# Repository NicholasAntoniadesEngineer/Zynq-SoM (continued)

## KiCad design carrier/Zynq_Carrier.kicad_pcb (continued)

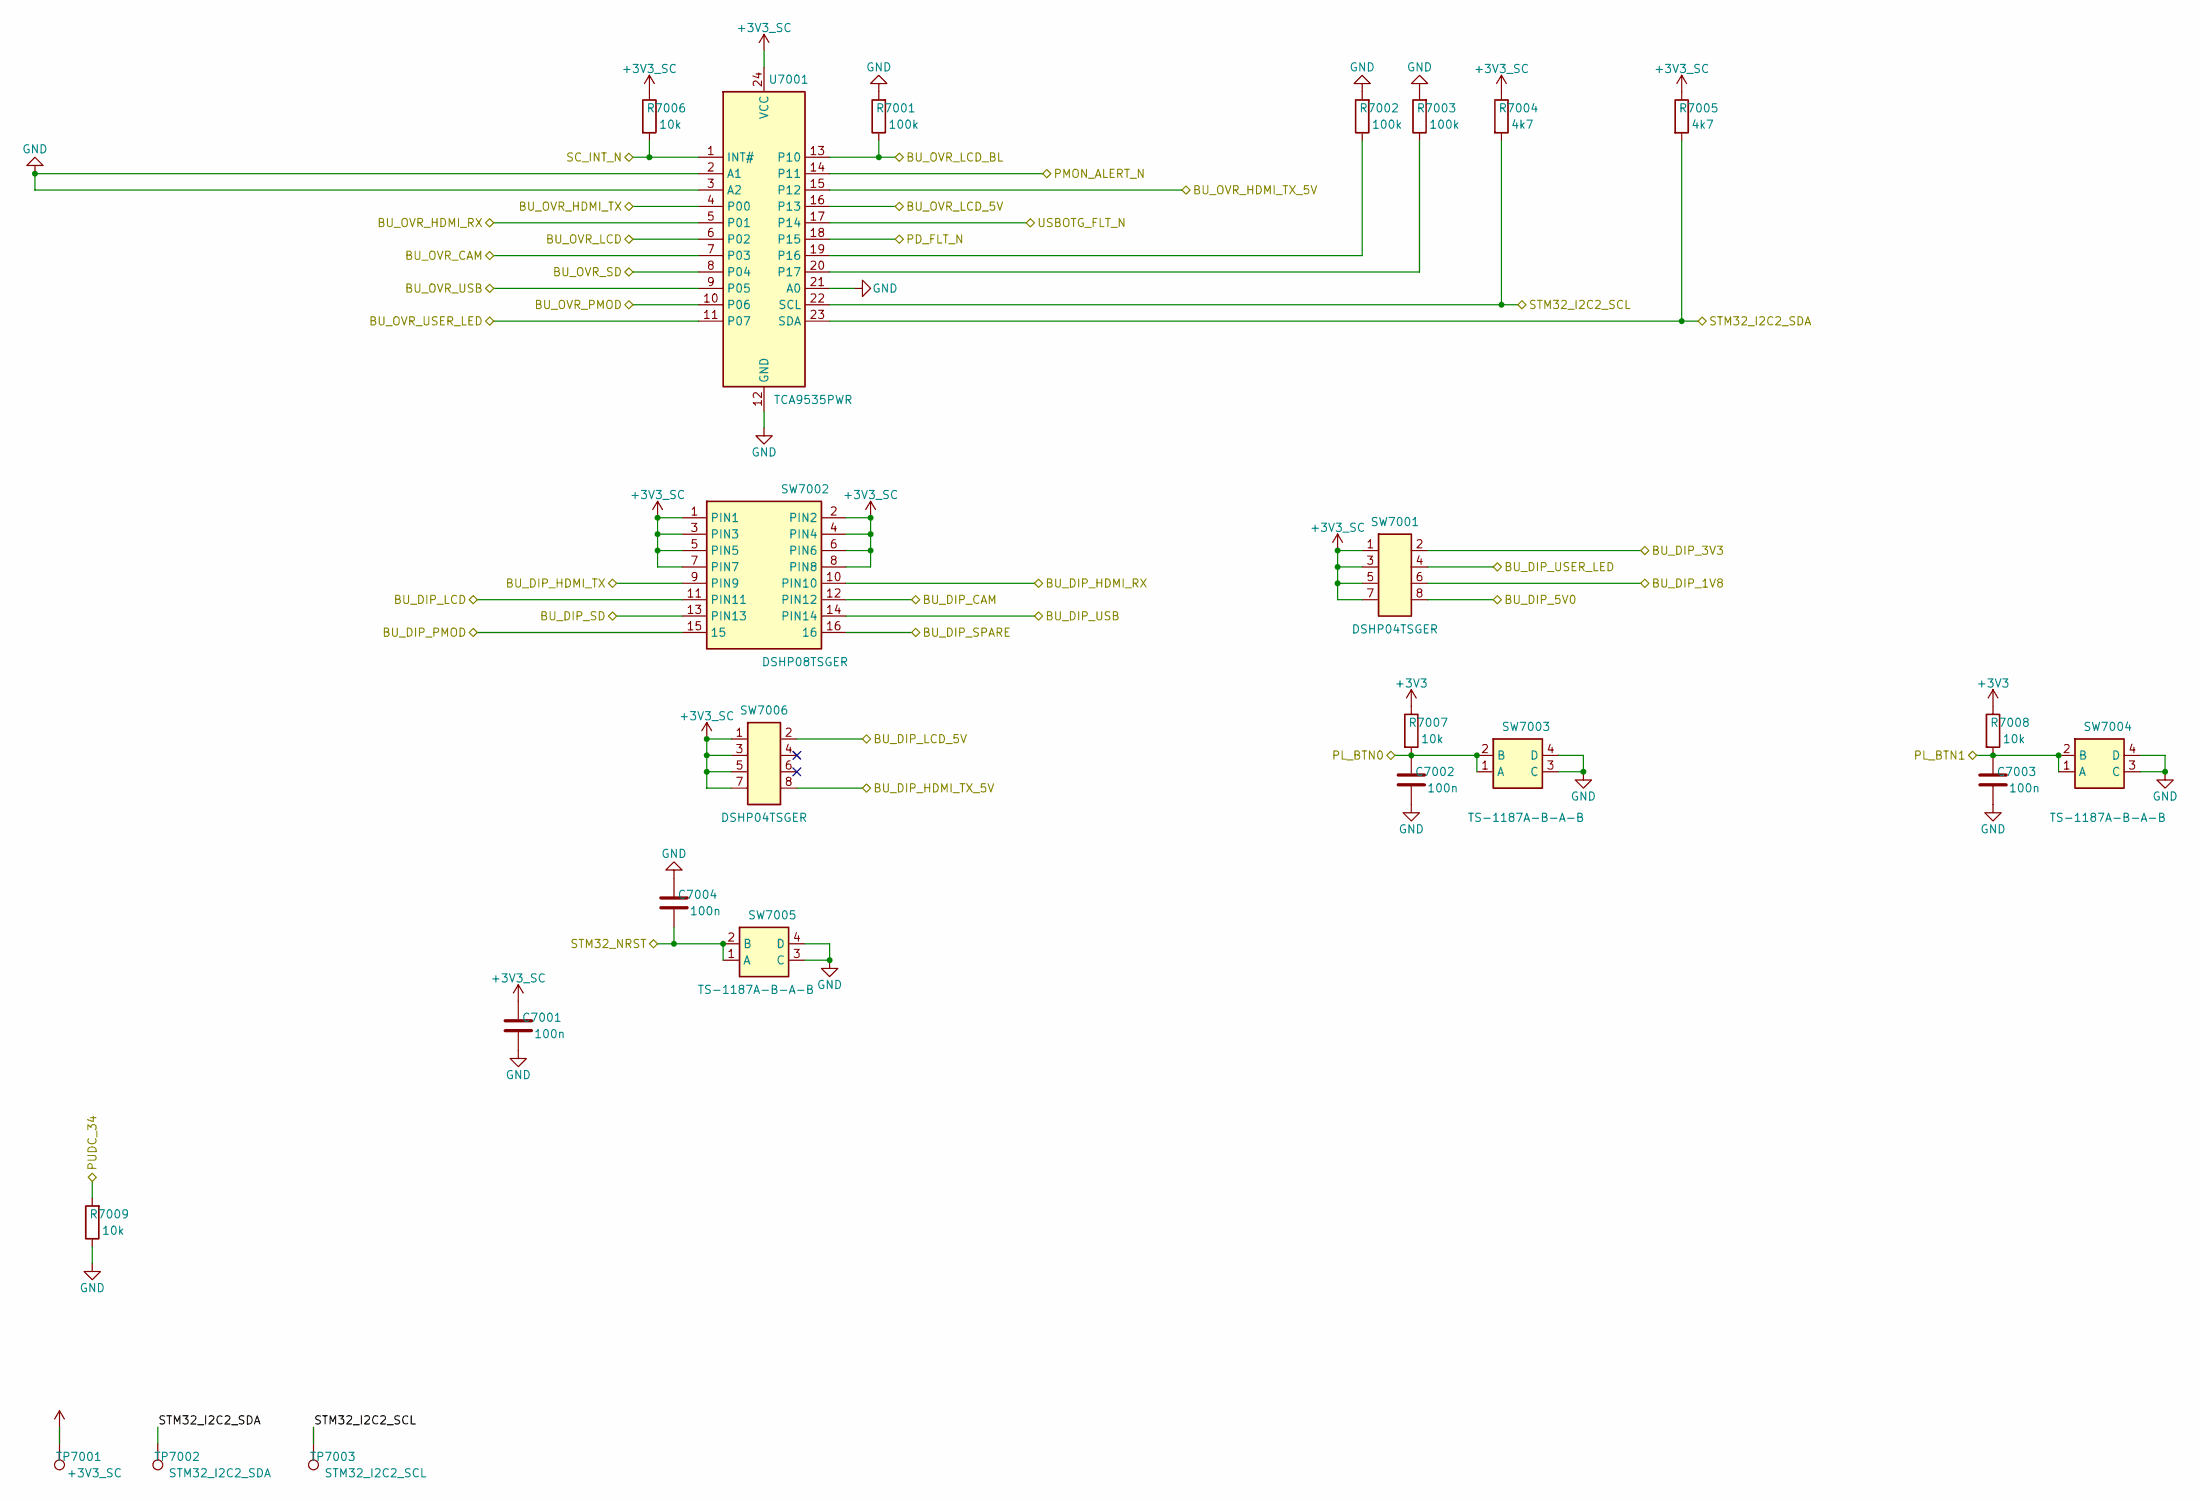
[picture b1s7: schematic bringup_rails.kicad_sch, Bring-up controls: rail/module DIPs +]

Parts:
C7001, C7002, C7003, C7004: 100n; C_0603_1608Metric; LCSC C14663
R7001, R7002, R7003: 100k; R_0603_1608Metric; LCSC C25803
R7004, R7005: 4k7; R_0603_1608Metric; LCSC C23162
R7006, R7007, R7008, R7009: 10k; R_0603_1608Metric; LCSC C25804
SW7001, SW7006: DSHP04TSGER; LCSC C3293144
SW7002: DSHP08TSGER; LCSC C3293147
SW7003, SW7004, SW7005: TS-1187A-B-A-B; LCSC C318884
TP7001: +3V3_SC; TestPoint_Pad_D1.5mm
TP7002: STM32_I2C2_SDA; TestPoint_Pad_D1.5mm
TP7003: STM32_I2C2_SCL; TestPoint_Pad_D1.5mm
U7001: TCA9535PWR; LCSC C130204

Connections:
+3V3: R7007.1, R7008.1; also elsewhere on the board
+3V3_SC: C7001.1, R7004.1, R7005.1, R7006.1, SW7001.1, SW7001.3, SW7001.5, SW7001.7, SW7002.1 (PIN1), SW7002.2 (PIN2), SW7002.3 (PIN3), SW7002.4 (PIN4), SW7002.5 (PIN5), SW7002.6 (PIN6), SW7002.7 (PIN7), SW7002.8 (PIN8), SW7006.1, SW7006.3, SW7006.5, SW7006.7, TP7001.1, U7001.24 (VCC); also elsewhere on the board
BU_DIP_1V8: SW7001.6; also elsewhere on the board
BU_DIP_3V3: SW7001.2; also elsewhere on the board
BU_DIP_5V0: SW7001.8; also elsewhere on the board
BU_DIP_CAM: SW7002.12 (PIN12); also elsewhere on the board
BU_DIP_HDMI_RX: SW7002.10 (PIN10); also elsewhere on the board
BU_DIP_HDMI_TX: SW7002.9 (PIN9); also elsewhere on the board
BU_DIP_HDMI_TX_5V: SW7006.8; also elsewhere on the board
BU_DIP_LCD: SW7002.11 (PIN11); also elsewhere on the board
BU_DIP_LCD_5V: SW7006.2; also elsewhere on the board
BU_DIP_PMOD: SW7002.15; also elsewhere on the board
BU_DIP_SD: SW7002.13 (PIN13); also elsewhere on the board
BU_DIP_SPARE: SW7002.16; also elsewhere on the board
BU_DIP_USB: SW7002.14 (PIN14); also elsewhere on the board
BU_DIP_USER_LED: SW7001.4; also elsewhere on the board
BU_OVR_CAM: U7001.7 (P03); also elsewhere on the board
BU_OVR_HDMI_RX: U7001.5 (P01); also elsewhere on the board
BU_OVR_HDMI_TX: U7001.4 (P00); also elsewhere on the board
BU_OVR_HDMI_TX_5V: U7001.15 (P12); also elsewhere on the board
BU_OVR_LCD: U7001.6 (P02); also elsewhere on the board
BU_OVR_LCD_5V: U7001.16 (P13); also elsewhere on the board
BU_OVR_LCD_BL: R7001.1, U7001.13 (P10); also elsewhere on the board
BU_OVR_PMOD: U7001.10 (P06); also elsewhere on the board
BU_OVR_SD: U7001.8 (P04); also elsewhere on the board
BU_OVR_USB: U7001.9 (P05); also elsewhere on the board
BU_OVR_USER_LED: U7001.11 (P07); also elsewhere on the board
GND: C7001.2, C7002.2, C7003.2, C7004.2, R7001.2, R7002.2, R7003.2, R7009.1, SW7003.3 (C), SW7003.4 (D), SW7004.3 (C), SW7004.4 (D), SW7005.3 (C), SW7005.4 (D), U7001.2 (A1), U7001.3 (A2), U7001.12 (GND), U7001.21 (A0); also elsewhere on the board
unnamed: R7002.1, U7001.19 (P16)
unnamed: R7003.1, U7001.20 (P17)
PD_FLT_N: U7001.18 (P15); also elsewhere on the board
PL_BTN0: C7002.1, R7007.2, SW7003.1 (A), SW7003.2 (B); also elsewhere on the board
PL_BTN1: C7003.1, R7008.2, SW7004.1 (A), SW7004.2 (B); also elsewhere on the board
PMON_ALERT_N: U7001.14 (P11); also elsewhere on the board
PUDC_34: R7009.2; also elsewhere on the board
SC_INT_N: R7006.2, U7001.1 (INT#); also elsewhere on the board
STM32_I2C2_SCL: R7004.2, TP7003.1, U7001.22 (SCL); also elsewhere on the board
STM32_I2C2_SDA: R7005.2, TP7002.1, U7001.23 (SDA); also elsewhere on the board
STM32_NRST: C7004.1, SW7005.1 (A), SW7005.2 (B); also elsewhere on the board
USBOTG_FLT_N: U7001.17 (P14); also elsewhere on the board

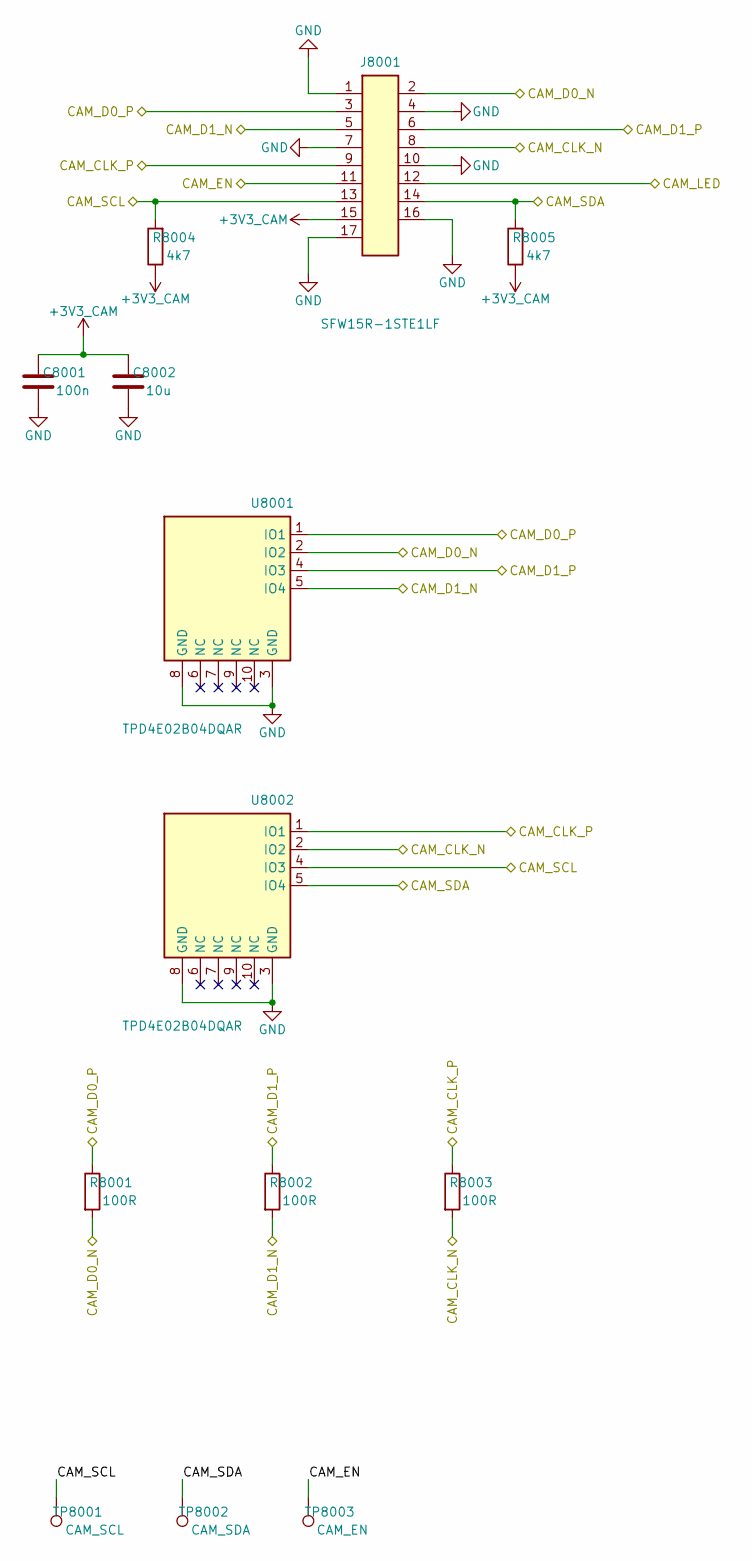
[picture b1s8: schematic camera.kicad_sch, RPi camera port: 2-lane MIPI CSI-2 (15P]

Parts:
C8001: 100n; C_0603_1608Metric; LCSC C14663
C8002: 10u; C_0805_2012Metric; LCSC C15850
J8001: SFW15R-1STE1LF; LCSC C3168538
R8001, R8002, R8003: 100R; R_0603_1608Metric; LCSC C22775
R8004, R8005: 4k7; R_0603_1608Metric; LCSC C23162
TP8001: CAM_SCL; TestPoint_Pad_D1.5mm
TP8002: CAM_SDA; TestPoint_Pad_D1.5mm
TP8003: CAM_EN; TestPoint_Pad_D1.5mm
U8001, U8002: TPD4E02B04DQAR; LCSC C106794

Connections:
+3V3_CAM: C8001.1, C8002.1, J8001.15, R8004.1, R8005.1; also elsewhere on the board
CAM_CLK_N: J8001.8, R8003.2, U8002.2 (IO2); also elsewhere on the board
CAM_CLK_P: J8001.9, R8003.1, U8002.1 (IO1); also elsewhere on the board
CAM_D0_N: J8001.2, R8001.2, U8001.2 (IO2); also elsewhere on the board
CAM_D0_P: J8001.3, R8001.1, U8001.1 (IO1); also elsewhere on the board
CAM_D1_N: J8001.5, R8002.2, U8001.5 (IO4); also elsewhere on the board
CAM_D1_P: J8001.6, R8002.1, U8001.4 (IO3); also elsewhere on the board
CAM_EN: J8001.11, TP8003.1; also elsewhere on the board
CAM_LED: J8001.12; also elsewhere on the board
CAM_SCL: J8001.13, R8004.2, TP8001.1, U8002.4 (IO3); also elsewhere on the board
CAM_SDA: J8001.14, R8005.2, TP8002.1, U8002.5 (IO4); also elsewhere on the board
GND: C8001.2, C8002.2, J8001.1, J8001.4, J8001.7, J8001.10, J8001.16, J8001.17, U8001.3 (GND), U8001.8 (GND), U8002.3 (GND), U8002.8 (GND); also elsewhere on the board

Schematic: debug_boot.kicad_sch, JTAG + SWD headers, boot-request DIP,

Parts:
J9001: 878311420; LCSC C240854
J9002: HX_JN1.27-2x5; HX_JN1.27-2x5_TP_H4.9; LCSC C42372555
R9001, R9002: 4k7; R_0603_1608Metric; LCSC C23162
R9003: 100R; R_0603_1608Metric; LCSC C22775
R9004, R9005, R9006: 10k; R_0603_1608Metric; LCSC C25804
SW9001: DIP-4; DSHP04TSGER; LCSC C3293144
SW9002: RESET; TS-1187A-B-A-B; LCSC C318884

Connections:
+3V3: J9001.2, R9001.1, R9002.1; also elsewhere on the board
+3V3_SC: J9002.1, R9003.1, R9004.1, R9005.1, R9006.1; also elsewhere on the board
GND: J9001.1, J9001.3, J9001.5, J9001.7, J9001.9, J9001.11, J9001.13, J9002.3, J9002.5, J9002.9, SW9001.5, SW9001.6, SW9001.7, SW9002.3 (C), SW9002.4 (D); also elsewhere on the board
unnamed: R9003.2, SW9001.8
unnamed: R9006.2, SW9001.4
STM32_BOOT0: SW9001.1; also elsewhere on the board
STM32_GPIO5: J9002.4; also elsewhere on the board
STM32_GPIO6: J9002.2; also elsewhere on the board
STM32_GPIO7: R9004.2, SW9001.2; also elsewhere on the board
STM32_GPIO8: R9005.2, SW9001.3; also elsewhere on the board
STM32_NRST: J9002.10, SW9002.1 (A), SW9002.2 (B); also elsewhere on the board
ZYNQ_TCK: J9001.6; also elsewhere on the board
ZYNQ_TDI: J9001.10, R9002.2; also elsewhere on the board
ZYNQ_TDO: J9001.8; also elsewhere on the board
ZYNQ_TMS: J9001.4, R9001.2; also elsewhere on the board

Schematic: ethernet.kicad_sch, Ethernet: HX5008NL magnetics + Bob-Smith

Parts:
C10001, C10002, C10003, C10004, C10005: 1n; C_1206_3225Metric; LCSC C9196
R10001, R10002, R10003, R10004: 75R; R_0603_1608Metric; LCSC C4275
T10001: HX5008NLT; LCSC C962544

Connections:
/ethernet/BS_COMMON: C10001.2, C10002.2, C10003.2, C10004.2, C10005.1, R10001.2, R10002.2, R10003.2, R10004.2
/ethernet/MCT1: C10001.1, R10001.1, T10001.24 (MCT1)
/ethernet/MCT2: C10002.1, R10002.1, T10001.21 (MCT2)
/ethernet/MCT3: C10003.1, R10003.1, T10001.18 (MCT3)
/ethernet/MCT4: C10004.1, R10004.1, T10001.15 (MCT4)
CHASSIS_GND: C10005.2; also elsewhere on the board
ETH_LINE_MDI_0_N: T10001.22 (MX1-); also elsewhere on the board
ETH_LINE_MDI_0_P: T10001.23 (MX1+); also elsewhere on the board
ETH_LINE_MDI_1_N: T10001.19 (MX2-); also elsewhere on the board
ETH_LINE_MDI_1_P: T10001.20 (MX2+); also elsewhere on the board
ETH_LINE_MDI_2_N: T10001.16 (MX3-); also elsewhere on the board
ETH_LINE_MDI_2_P: T10001.17 (MX3+); also elsewhere on the board
ETH_LINE_MDI_3_N: T10001.13 (MX4-); also elsewhere on the board
ETH_LINE_MDI_3_P: T10001.14 (MX4+); also elsewhere on the board
ETH_PHY_MDI0_N: T10001.3 (TD1-); also elsewhere on the board
ETH_PHY_MDI0_P: T10001.2 (TD1+); also elsewhere on the board
ETH_PHY_MDI1_N: T10001.6 (TD2-); also elsewhere on the board
ETH_PHY_MDI1_P: T10001.5 (TD2+); also elsewhere on the board
ETH_PHY_MDI2_N: T10001.9 (TD3-); also elsewhere on the board
ETH_PHY_MDI2_P: T10001.8 (TD3+); also elsewhere on the board
ETH_PHY_MDI3_N: T10001.12 (TD4-); also elsewhere on the board
ETH_PHY_MDI3_P: T10001.11 (TD4+); also elsewhere on the board

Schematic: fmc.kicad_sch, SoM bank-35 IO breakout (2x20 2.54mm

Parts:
C11001, C11004: 10u; C_0805_2012Metric; LCSC C15850
C11002, C11005: 100n; C_0603_1608Metric; LCSC C14663
C11003: 1u; C_0603_1608Metric; LCSC C15849
J11001: Header_2x20_2.54mm; PinHeader_2x20_P2.54mm_Vertical
TP11001: +2V5_VADJ; TestPoint_Pad_D1.5mm
U11001: TLV75725PDYDR; LCSC C35209004

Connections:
+2V5_VADJ: C11004.1, C11005.1, J11001.2, TP11001.1, U11001.5 (OUT); also elsewhere on the board
+3V3: C11001.1, C11002.1, C11003.1, J11001.1, U11001.1 (IN), U11001.3 (EN); also elsewhere on the board
FMC_CLK0_M2C_N: J11001.4; also elsewhere on the board
FMC_CLK0_M2C_P: J11001.3; also elsewhere on the board
FMC_CLK1_M2C_N: J11001.6; also elsewhere on the board
FMC_CLK1_M2C_P: J11001.5; also elsewhere on the board
FMC_LA00_CC_N: J11001.10; also elsewhere on the board
FMC_LA00_CC_P: J11001.9; also elsewhere on the board
FMC_LA01_CC_N: J11001.12; also elsewhere on the board
FMC_LA01_CC_P: J11001.11; also elsewhere on the board
FMC_LA02_N: J11001.14; also elsewhere on the board
FMC_LA02_P: J11001.13; also elsewhere on the board
FMC_LA03_N: J11001.18; also elsewhere on the board
FMC_LA03_P: J11001.17; also elsewhere on the board
FMC_LA04_N: J11001.20; also elsewhere on the board
FMC_LA04_P: J11001.19; also elsewhere on the board
FMC_LA05_N: J11001.22; also elsewhere on the board
FMC_LA05_P: J11001.21; also elsewhere on the board
FMC_LA06_N: J11001.26; also elsewhere on the board
FMC_LA06_P: J11001.25; also elsewhere on the board
FMC_LA07_N: J11001.28; also elsewhere on the board
FMC_LA07_P: J11001.27; also elsewhere on the board
FMC_LA08_N: J11001.30; also elsewhere on the board
FMC_LA08_P: J11001.29; also elsewhere on the board
FMC_LA09_N: J11001.34; also elsewhere on the board
FMC_LA09_P: J11001.33; also elsewhere on the board
FMC_LA10_N: J11001.36; also elsewhere on the board
FMC_LA10_P: J11001.35; also elsewhere on the board
FMC_LA11_N: J11001.38; also elsewhere on the board
FMC_LA11_P: J11001.37; also elsewhere on the board
GND: C11001.2, C11002.2, C11003.2, C11004.2, C11005.2, J11001.7, J11001.8, J11001.15, J11001.16, J11001.23, J11001.24, J11001.31, J11001.32, J11001.39, J11001.40, U11001.2 (GND), U11001.6 (EP); also elsewhere on the board

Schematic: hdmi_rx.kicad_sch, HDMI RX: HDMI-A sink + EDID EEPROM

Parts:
C12001: 100n; C_0603_1608Metric; LCSC C14663
J12001: HDMI-019S; LCSC C111617
R12001: 1k; R_0603_1608Metric; LCSC C21190
R12002: 27k; R_0603_1608Metric; LCSC C22967
R12003: 10k; R_0603_1608Metric; LCSC C25804
R12004: 15k; R_0603_1608Metric; LCSC C22809
U12001: M24C02-WMN6TP; MPN M24C02-WMN6TP; LCSC C7562
U12002, U12003: TPD4E02B04DQAR; LCSC C106794
U12004: TPD4E05U06DQAR; LCSC C138714

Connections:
+3V3_HDMI_RX: R12002.1; also elsewhere on the board
/hdmi_rx/HDMI_RX_5V: C12001.1, J12001.18 (+5V), R12001.1, R12003.1, U12001.7 (~WC), U12001.8 (VCC)
/hdmi_rx/HDMI_RX_HPD: J12001.19 (HOT_PLUG_DET), R12001.2, U12004.5 (D2-)
/hdmi_rx/HDMI_RX_SCL: J12001.15 (I2C-CLK), U12001.6 (SCL), U12004.1 (D1+)
/hdmi_rx/HDMI_RX_SDA: J12001.16 (I2C_DATA), U12001.5 (SDA), U12004.2 (D1-)
CHASSIS_GND: J12001.20 (SHD), J12001.21 (SHD), J12001.22 (SHD), J12001.23 (SHD); also elsewhere on the board
GND: C12001.2, J12001.2 (D2_SHIELD), J12001.5 (D1_SHIELD), J12001.8 (D0_SHIELD), J12001.11 (CK_SHIELD), J12001.17 (GND), R12004.2, U12001.1 (E0), U12001.2 (E1), U12001.3 (E2), U12001.4 (VSS), U12002.3 (GND), U12002.8 (GND), U12003.3 (GND), U12003.8 (GND), U12004.3 (GND), U12004.8 (GND); also elsewhere on the board
HDMI_RX_5V_DET: R12003.2, R12004.1; also elsewhere on the board
HDMI_RX_CEC: J12001.13 (CEC), R12002.2, U12004.4 (D2+); also elsewhere on the board
HDMI_RX_CLK_N: J12001.12 (CK-), U12003.5 (IO4); also elsewhere on the board
HDMI_RX_CLK_P: J12001.10 (CK+), U12003.4 (IO3); also elsewhere on the board
HDMI_RX_D0_N: J12001.9 (D0-), U12003.2 (IO2); also elsewhere on the board
HDMI_RX_D0_P: J12001.7 (D0+), U12003.1 (IO1); also elsewhere on the board
HDMI_RX_D1_N: J12001.6 (D1-), U12002.5 (IO4); also elsewhere on the board
HDMI_RX_D1_P: J12001.4 (D1+), U12002.4 (IO3); also elsewhere on the board
HDMI_RX_D2_N: J12001.3 (D2-), U12002.2 (IO2); also elsewhere on the board
HDMI_RX_D2_P: J12001.1 (D2+), U12002.1 (IO1); also elsewhere on the board

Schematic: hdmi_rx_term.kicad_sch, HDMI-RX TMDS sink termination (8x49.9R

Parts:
C13001: 100n; C_0603_1608Metric; LCSC C14663
C13002: 1u; C_0603_1608Metric; LCSC C15849
R13001, R13002, R13003, R13004, R13005, R13006, R13007, R13008: 49.9R; R_0603_1608Metric; LCSC C114625

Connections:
+3V3: C13001.1, C13002.1, R13001.2, R13002.2, R13003.2, R13004.2, R13005.2, R13006.2, R13007.2, R13008.2; also elsewhere on the board
GND: C13001.2, C13002.2; also elsewhere on the board
HDMI_RX_CLK_N: R13008.1; also elsewhere on the board
HDMI_RX_CLK_P: R13007.1; also elsewhere on the board
HDMI_RX_D0_N: R13006.1; also elsewhere on the board
HDMI_RX_D0_P: R13005.1; also elsewhere on the board
HDMI_RX_D1_N: R13004.1; also elsewhere on the board
HDMI_RX_D1_P: R13003.1; also elsewhere on the board
HDMI_RX_D2_N: R13002.1; also elsewhere on the board
HDMI_RX_D2_P: R13001.1; also elsewhere on the board

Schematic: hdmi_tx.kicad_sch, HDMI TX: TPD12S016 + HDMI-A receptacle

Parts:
C14001, C14002, C14003: 100n; C_0603_1608Metric; LCSC C14663
C14004: 1u; C_0603_1608Metric; LCSC C15849
C14005: 10u; C_0805_2012Metric; LCSC C15850
J14001: HDMI-019S; LCSC C111617
R14001, R14002: 10k; R_0603_1608Metric; LCSC C25804
TP14001: +5V_HDMI_TX; TestPoint_Pad_D1.5mm
TP14002: ZYNQ_HDMI_TX_SCL; TestPoint_Pad_D1.5mm
TP14003: ZYNQ_HDMI_TX_SDA; TestPoint_Pad_D1.5mm
U14001: TPD12S016PWR; LCSC C201665

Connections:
+3V3_HDMI_TX: C14001.1, C14005.1, R14001.1, R14002.1, U14001.24 (VCCA); also elsewhere on the board
+5V_HDMI_TX: C14002.1, TP14001.1, U14001.11 (VCC5V); also elsewhere on the board
/hdmi_tx/HDMI_TX_CON_5V0: C14003.1, C14004.1, J14001.18 (+5V), U14001.13 (5V_OUT)
/hdmi_tx/HDMI_TX_CON_CEC: J14001.13 (CEC), U14001.7 (CEC_B)
/hdmi_tx/HDMI_TX_CON_HPD: J14001.19 (HOT_PLUG_DET), U14001.10 (HPD_B-)
/hdmi_tx/HDMI_TX_CON_SCL: J14001.15 (I2C-CLK), U14001.8 (SCL_B)
/hdmi_tx/HDMI_TX_CON_SDA: J14001.16 (I2C_DATA), U14001.9 (SDA_B)
CHASSIS_GND: J14001.20 (SHD), J14001.21 (SHD), J14001.22 (SHD), J14001.23 (SHD); also elsewhere on the board
GND: C14001.2, C14002.2, C14003.2, C14004.2, C14005.2, J14001.2 (D2_SHIELD), J14001.5 (D1_SHIELD), J14001.8 (D0_SHIELD), J14001.11 (CK_SHIELD), J14001.17 (GND), U14001.6 (GND), U14001.14 (GND), U14001.19 (GND); also elsewhere on the board
unnamed: R14002.2, U14001.12 (CT_HPD)
unnamed: R14001.2, U14001.5 (LS_OE)
ZYNQ_HDMI_TX_CEC: U14001.1 (CEC_A); also elsewhere on the board
ZYNQ_HDMI_TX_HPD: U14001.4 (HPD_A-); also elsewhere on the board
ZYNQ_HDMI_TX_SCL: TP14002.1, U14001.2 (SCL_A); also elsewhere on the board
ZYNQ_HDMI_TX_SDA: TP14003.1, U14001.3 (SDA_A); also elsewhere on the board
ZYNQ_HDMI_TX_TMDS_0_N: J14001.9 (D0-), U14001.17 (D0-); also elsewhere on the board
ZYNQ_HDMI_TX_TMDS_0_P: J14001.7 (D0+), U14001.18 (D0+); also elsewhere on the board
ZYNQ_HDMI_TX_TMDS_1_N: J14001.6 (D1-), U14001.20 (D1-); also elsewhere on the board
ZYNQ_HDMI_TX_TMDS_1_P: J14001.4 (D1+), U14001.21 (D1+); also elsewhere on the board
ZYNQ_HDMI_TX_TMDS_2_N: J14001.3 (D2-), U14001.22 (D2-); also elsewhere on the board
ZYNQ_HDMI_TX_TMDS_2_P: J14001.1 (D2+), U14001.23 (D2+); also elsewhere on the board
ZYNQ_HDMI_TX_TMDS_CLK_N: J14001.12 (CK-), U14001.15 (CLK-); also elsewhere on the board
ZYNQ_HDMI_TX_TMDS_CLK_P: J14001.10 (CK+), U14001.16 (CLK+); also elsewhere on the board

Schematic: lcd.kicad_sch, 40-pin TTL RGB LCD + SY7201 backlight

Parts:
C15001, C15004: 10u; C_0805_2012Metric; LCSC C15850
C15002: 2.2u; C_0805_2012Metric; LCSC C125847
C15003: 100n; C_0603_1608Metric; LCSC C14663
C15005: 1u; C_0603_1608Metric; LCSC C15849
D15001: SS34; D_SMA; LCSC C8678
J15001: AFC07-S40FCA-00; LCSC C262572
L15001: 10uH; SWPA4030S100MT; LCSC C38117
R15001: 1.5R; R_0603_1608Metric; LCSC C22769
R15002, R15003: 4k7; R_0603_1608Metric; LCSC C23162
R15004, R15005: 100k; R_0603_1608Metric; LCSC C25803
R15006: 10k; R_0603_1608Metric; LCSC C25804
R15007: 22R; R_0603_1608Metric; LCSC C23345
TP15001: +5V_LCD; TestPoint_Pad_D1.5mm
TP15002: LCD_CTP_SDA; TestPoint_Pad_D1.5mm
TP15003: LCD_CTP_SCL; TestPoint_Pad_D1.5mm
U15001: SY7201ABC; LCSC C82173
U15002: USBLC6-2SC6; LCSC C7519

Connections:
+3V3: U15002.5; also elsewhere on the board
+3V3_LCD: C15003.1, C15004.1, J15001.4, R15002.2, R15003.2, R15006.2; also elsewhere on the board
+5V_LCD: C15001.1, C15005.1, L15001.1, TP15001.1, U15001.6 (IN); also elsewhere on the board
/lcd/CTP_SCL_FFC: J15001.38, U15002.3
/lcd/CTP_SDA_FFC: J15001.37, U15002.1
/lcd/LCD_VLED_N: J15001.1, R15001.1, U15001.3 (FB)
/lcd/LCD_VLED_P: C15002.1, D15001.1 (K), J15001.2, U15001.5 (OVP)
GND: C15001.2, C15002.2, C15003.2, C15004.2, C15005.2, J15001.3, J15001.29, J15001.36, R15001.2, R15004.2, R15005.2, U15001.2 (GND), U15002.2; also elsewhere on the board
LCD_B0: J15001.21; also elsewhere on the board
LCD_B1: J15001.22; also elsewhere on the board
LCD_B2: J15001.23; also elsewhere on the board
LCD_B3: J15001.24; also elsewhere on the board
LCD_B4: J15001.25; also elsewhere on the board
LCD_B5: J15001.26; also elsewhere on the board
LCD_B6: J15001.27; also elsewhere on the board
LCD_B7: J15001.28; also elsewhere on the board
LCD_BL_PWM: R15004.1, U15001.4 (EN/PWM); also elsewhere on the board
LCD_CTP_INT: J15001.40; also elsewhere on the board
LCD_CTP_RST: J15001.39, R15005.1; also elsewhere on the board
LCD_CTP_SCL: R15003.1, TP15003.1, U15002.4; also elsewhere on the board
LCD_CTP_SDA: R15002.1, TP15002.1, U15002.6; also elsewhere on the board
LCD_DE: J15001.34; also elsewhere on the board
LCD_DISP: J15001.31, R15006.1; also elsewhere on the board
LCD_G0: J15001.13; also elsewhere on the board
LCD_G1: J15001.14; also elsewhere on the board
LCD_G2: J15001.15; also elsewhere on the board
LCD_G3: J15001.16; also elsewhere on the board
LCD_G4: J15001.17; also elsewhere on the board
LCD_G5: J15001.18; also elsewhere on the board
LCD_G6: J15001.19; also elsewhere on the board
LCD_G7: J15001.20; also elsewhere on the board
LCD_HSYNC: J15001.32; also elsewhere on the board
LCD_PCLK: R15007.2; also elsewhere on the board
LCD_R0: J15001.5; also elsewhere on the board
LCD_R1: J15001.6; also elsewhere on the board
LCD_R2: J15001.7; also elsewhere on the board
LCD_R3: J15001.8; also elsewhere on the board
LCD_R4: J15001.9; also elsewhere on the board
LCD_R5: J15001.10; also elsewhere on the board
LCD_R6: J15001.11; also elsewhere on the board
LCD_R7: J15001.12; also elsewhere on the board
LCD_VSYNC: J15001.33; also elsewhere on the board
unnamed: D15001.2 (A), L15001.2, U15001.1 (LX)
unnamed: J15001.30, R15007.1

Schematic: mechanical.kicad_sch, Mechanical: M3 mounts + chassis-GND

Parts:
H34001, H34002, H34003, H34004: MountingHole_M3; MountingHole_3.2mm_M3_Pad

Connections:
CHASSIS_GND: H34001.1, H34002.1, H34003.1, H34004.1; also elsewhere on the board

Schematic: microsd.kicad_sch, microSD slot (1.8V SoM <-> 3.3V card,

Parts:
C16001, C16002, C16004: 100n; C_0603_1608Metric; LCSC C14663
C16003: 22u; C_0805_2012Metric; LCSC C45783
J16001: TF-01A; LCSC C91145
R16001, R16002, R16003, R16004, R16005: 100k; R_0603_1608Metric; LCSC C25803
R16006: 10k; R_0603_1608Metric; LCSC C25804
TP16001: SDIO_CMD; TestPoint_Pad_D1.5mm
TP16002: SDIO_CLK; TestPoint_Pad_D1.5mm
U16001: TXS02612RTWR; LCSC C140276
U16002: TPD6E001RSER; LCSC C1973318

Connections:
+1V8: C16001.1, U16001.5 (VCCA); also elsewhere on the board
+3V3_SD: C16002.1, C16003.1, C16004.1, J16001.4 (VDD), R16001.1, R16002.1, R16003.1, R16004.1, R16005.1, R16006.1, U16001.17 (VCCB1), U16001.21 (VCCB0), U16002.10 (VCC); also elsewhere on the board
/microsd/SD_CARD_CLK: J16001.5 (CLK(SCLK)), U16001.19 (CLKB0), U16002.1 (IO1)
/microsd/SD_CARD_CMD: J16001.3 (CMD(DI)), R16001.2, U16001.20 (CMDB0), U16002.2 (IO2)
/microsd/SD_CARD_D0: J16001.7 (DAT0(D0)), R16002.2, U16001.18 (DAT0B0), U16002.3 (IO3)
/microsd/SD_CARD_D1: J16001.8 (DAT1(RSV)), R16003.2, U16001.16 (DAT1B0), U16002.6 (IO4)
/microsd/SD_CARD_D2: J16001.1 (DAT2(RSV)), R16004.2, U16001.23 (DAT2B0), U16002.7 (IO5)
/microsd/SD_CARD_D3: J16001.2 (CDDAT3(CS)), R16005.2, U16001.22 (DAT3B0), U16002.8 (IO6)
GND: C16001.2, C16002.2, C16003.2, C16004.2, J16001.6 (VSS), J16001.10 (GND), J16001.11 (GND), J16001.12 (GND), J16001.13 (GND), U16001.2 (GND), U16001.11 (GND), U16001.24 (SEL), U16001.25 (EP), U16002.5 (GND); also elsewhere on the board
SDIO_CLK: TP16002.1, U16001.9 (CLKA); also elsewhere on the board
SDIO_CMD: TP16001.1, U16001.4 (CMDA); also elsewhere on the board
SDIO_D0: U16001.6 (DAT0A); also elsewhere on the board
SDIO_D1: U16001.7 (DAT1A); also elsewhere on the board
SDIO_D2: U16001.1 (DAT2A); also elsewhere on the board
SDIO_D3: U16001.3 (DAT3A); also elsewhere on the board
SD_CARD_DETECT: J16001.9 (CD), R16006.2; also elsewhere on the board

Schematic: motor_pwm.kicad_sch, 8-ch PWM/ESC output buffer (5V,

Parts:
C36001, C36002: 100n; C_0603_1608Metric; LCSC C14663
C36003: 10u; C_0805_2012Metric; LCSC C15850
D36001, D36002: SRV05-4; SOT-23-6; LCSC C2836319
J36001: HX PZ2.54-3x8P ZZ; HX_PZ2.54-3x8P_ZZ; LCSC C32713295
R36001: 10k; R_0603_1608Metric; LCSC C25804
R36002: 13k; R_0603_1608Metric; LCSC C22797
RN36001, RN36002: 4D03WGJ0330T5E; LCSC C25508
TP36001: +5V_MOTOR_IO; TestPoint_Pad_D1.5mm
U36001: SN74HCT245PWR; LCSC C6779
U36003: SY6280AAC; LCSC C55136

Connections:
+5V: C36001.1, C36002.1, D36001.5 (VP), D36002.5 (VP), R36001.1, U36001.1 (DIR), U36001.20 (VCC), U36003.4 (EN), U36003.5 (IN); also elsewhere on the board
+5V_MOTOR_IO: C36003.1, J36001.9, J36001.10, J36001.11, J36001.12, J36001.13, J36001.14, J36001.15, J36001.16, TP36001.1, U36003.1 (OUT)
/motor_pwm/ESC_OUT0: D36001.1 (IO1), J36001.1, RN36001.8
/motor_pwm/ESC_OUT1: D36001.3 (IO2), J36001.2, RN36001.7
/motor_pwm/ESC_OUT2: D36001.4 (IO3), J36001.3, RN36001.6
/motor_pwm/ESC_OUT3: D36001.6 (IO4), J36001.4, RN36001.5
/motor_pwm/ESC_OUT4: D36002.1 (IO1), J36001.5, RN36002.8
/motor_pwm/ESC_OUT5: D36002.3 (IO2), J36001.6, RN36002.7
/motor_pwm/ESC_OUT6: D36002.4 (IO3), J36001.7, RN36002.6
/motor_pwm/ESC_OUT7: D36002.6 (IO4), J36001.8, RN36002.5
/motor_pwm/ESC_SIG0: RN36001.1, U36001.18 (B1)
/motor_pwm/ESC_SIG1: RN36001.2, U36001.17 (B2)
/motor_pwm/ESC_SIG2: RN36001.3, U36001.16 (B3)
/motor_pwm/ESC_SIG3: RN36001.4, U36001.15 (B4)
/motor_pwm/ESC_SIG4: RN36002.1, U36001.14 (B5)
/motor_pwm/ESC_SIG5: RN36002.2, U36001.13 (B6)
/motor_pwm/ESC_SIG6: RN36002.3, U36001.12 (B7)
/motor_pwm/ESC_SIG7: RN36002.4, U36001.11 (B8)
ESC_BUF_OE_N: R36001.2, U36001.19 (#OE); also elsewhere on the board
ESC_PWM_IN0: U36001.2 (A1); also elsewhere on the board
ESC_PWM_IN1: U36001.3 (A2); also elsewhere on the board
ESC_PWM_IN2: U36001.4 (A3); also elsewhere on the board
ESC_PWM_IN3: U36001.5 (A4); also elsewhere on the board
ESC_PWM_IN4: U36001.6 (A5); also elsewhere on the board
ESC_PWM_IN5: U36001.7 (A6); also elsewhere on the board
ESC_PWM_IN6: U36001.8 (A7); also elsewhere on the board
ESC_PWM_IN7: U36001.9 (A8); also elsewhere on the board
GND: C36001.2, C36002.2, C36003.2, D36001.2 (VN), D36002.2 (VN), J36001.17, J36001.18, J36001.19, J36001.20, J36001.21, J36001.22, J36001.23, J36001.24, R36002.2, U36001.10 (GND), U36003.2 (GND); also elsewhere on the board
unnamed: R36002.1, U36003.3 (ISET)

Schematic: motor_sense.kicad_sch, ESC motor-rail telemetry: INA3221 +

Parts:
C37001, C37002: 100n; C_0603_1608Metric; LCSC C14663
C37003: 10u; C_0805_2012Metric; LCSC C15850
C37004: 470uF/35V; CP_Elec_10x10.5; LCSC C976030
D37001: SMBJ28A; LCSC C42440491
J37002, J37003: XT60PW-M; LCSC C98732
R37001: 10k; R_0603_1608Metric; LCSC C25804
RS37001: 10mR; RLM12FTCMR010; LCSC C188070
U37002: INA3221AIRGVR; LCSC C181255

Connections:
+3V3_SC: C37002.1, C37003.1, R37001.1, U37002.4 (VS), U37002.16 (VPU); also elsewhere on the board
/motor_sense/ESC_VRAIL: C37004.1, J37003.2 (+), RS37001.2, U37002.11 (IN-1)
/motor_sense/ESC_VRAIL_IN: C37001.1, D37001.1 (K), J37002.2 (+), RS37001.1, U37002.12 (IN+1)
ESC_FAULT_N: R37001.2, U37002.9 (CRITICAL); also elsewhere on the board
GND: C37001.2, C37002.2, C37003.2, C37004.2, D37001.2 (A), J37002.1 (-), J37002.3, J37002.4, J37003.1 (-), J37003.3, J37003.4, U37002.1 (IN-3), U37002.2 (IN+3), U37002.3 (GND), U37002.14 (IN-2), U37002.15 (IN+2), U37002.17 (PAD); also elsewhere on the board
STM32_I2C2_SCL: U37002.6 (SCL); also elsewhere on the board
STM32_I2C2_SDA: U37002.5 (A0), U37002.7 (SDA); also elsewhere on the board

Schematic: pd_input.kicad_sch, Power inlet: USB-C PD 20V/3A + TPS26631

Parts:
C17001: 100n; C_0603_1608Metric; LCSC C14663
C17002: 10u; C_1210_3225Metric; LCSC C596319
C17003: 47n; C_0603_1608Metric; LCSC C1622
D17001: SMBJ22A; D_SMB; LCSC C10214
J17001: TYPE-C-31-M-12; LCSC C165948
R17003, R17006: 100k; R_0603_1608Metric; LCSC C25803
R17004: 5.49k; R_0603_1608Metric; LCSC C188263
R17005: 5.1k; R_0603_1608Metric; LCSC C23186
TP17001: +VBUS_IN; TestPoint_Pad_D1.5mm
TP17002: +VIN; TestPoint_Pad_D1.5mm
U17001: TPS26631PWPR; LCSC C2866319
U17002: USBLC6-2SC6; LCSC C7519

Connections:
+3V3_SC: R17006.1, U17002.5; also elsewhere on the board
+VBUS_IN: C17001.1, D17001.1 (K), J17001.A4B9 (VBUS), J17001.B4A9 (VBUS), R17003.1, TP17001.1, U17001.1 (IN), U17001.2 (IN), U17001.3 (IN), U17001.6 (IN_SYS), U17001.7 (UVLO); also elsewhere on the board
+VIN: C17002.1, TP17002.1, U17001.18 (OUT), U17001.19 (OUT), U17001.20 (OUT); also elsewhere on the board
/pd_input/PD_USB_DN_CONN: J17001.A7 (DN1), J17001.B7 (DN2), U17002.3
/pd_input/PD_USB_DP_CONN: J17001.A6 (DP1), J17001.B6 (DP2), U17002.1
CHASSIS_GND: J17001.1 (EH), J17001.2 (EH), J17001.3 (EH), J17001.4 (EH); also elsewhere on the board
GND: C17001.2, C17002.2, C17003.2, D17001.2 (A), J17001.A1B12 (GND), J17001.B1A12 (GND), R17004.2, R17005.2, U17001.9 (GND), U17001.12 (MODE), U17001.16 (PGTH), U17001.21 (EP), U17002.2; also elsewhere on the board
unnamed: R17005.1, U17001.11 (ILIM)
unnamed: R17003.2, R17004.1, U17001.8 (OVP)
unnamed: C17003.1, U17001.10 (dVdT)
PD_FLT_N: R17006.2, U17001.15 (FLT#); also elsewhere on the board
STM32_USB_CC1: J17001.A5 (CC1); also elsewhere on the board
STM32_USB_CC2: J17001.B5 (CC2); also elsewhere on the board
STM32_USB_D_N: U17002.4; also elsewhere on the board
STM32_USB_D_P: U17002.6; also elsewhere on the board

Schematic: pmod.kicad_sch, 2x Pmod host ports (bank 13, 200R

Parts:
C18001, C18003: 100n; C_0603_1608Metric; LCSC C14663
C18002, C18004: 10u; C_0805_2012Metric; LCSC C15850
J18001, J18002: DS1024-2x6R2; LCSC C49284652
R18001, R18002, R18003, R18004, R18005, R18006, R18007, R18008, R18009, R18010, R18011, R18012, R18013, R18014, R18015, R18016: 200R; R_0603_1608Metric; LCSC C8218
U18001, U18002, U18003, U18004: TPD4E1U06; TPD4E1U06DBVR; LCSC C124691

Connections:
+3V3_PMOD: C18001.1, C18002.1, C18003.1, C18004.1, J18001.11, J18001.12, J18002.11, J18002.12; also elsewhere on the board
GND: C18001.2, C18002.2, C18003.2, C18004.2, J18001.9, J18001.10, J18002.9, J18002.10, U18001.2 (GND), U18002.2 (GND), U18003.2 (GND), U18004.2 (GND); also elsewhere on the board
IO_L2_N_13: R18002.1, U18001.3 (D2+); also elsewhere on the board
IO_L2_P_13: R18001.1, U18001.1 (D1+); also elsewhere on the board
IO_L3_N_13: R18004.1, U18001.4 (D2-); also elsewhere on the board
IO_L3_P_13: R18003.1, U18001.6 (D1-); also elsewhere on the board
IO_L4_N_13: R18006.1, U18002.3 (D2+); also elsewhere on the board
IO_L4_P_13: R18005.1, U18002.1 (D1+); also elsewhere on the board
IO_L5P_13: R18007.1, U18002.6 (D1-); also elsewhere on the board
IO_L5_N_13: R18008.1, U18002.4 (D2-); also elsewhere on the board
IO_L7_N_13: R18010.1, U18003.3 (D2+); also elsewhere on the board
IO_L7_P_13: R18009.1, U18003.1 (D1+); also elsewhere on the board
IO_L8_N_13: R18012.1, U18003.4 (D2-); also elsewhere on the board
IO_L8_P_13: R18011.1, U18003.6 (D1-); also elsewhere on the board
IO_L9_DQS_N_13: R18014.1, U18004.3 (D2+); also elsewhere on the board
IO_L9_DQS_P_13: R18013.1, U18004.1 (D1+); also elsewhere on the board
IO_L10_N_13: R18016.1, U18004.4 (D2-); also elsewhere on the board
IO_L10_P_13: R18015.1, U18004.6 (D1-); also elsewhere on the board
unnamed: J18001.1, R18001.2
unnamed: J18001.2, R18005.2
unnamed: J18001.3, R18002.2
unnamed: J18001.4, R18006.2
unnamed: J18001.5, R18003.2
unnamed: J18001.6, R18007.2
unnamed: J18001.7, R18004.2
unnamed: J18001.8, R18008.2
unnamed: J18002.1, R18009.2
unnamed: J18002.2, R18013.2
unnamed: J18002.3, R18010.2
unnamed: J18002.4, R18014.2
unnamed: J18002.5, R18011.2
unnamed: J18002.6, R18015.2
unnamed: J18002.7, R18012.2
unnamed: J18002.8, R18016.2

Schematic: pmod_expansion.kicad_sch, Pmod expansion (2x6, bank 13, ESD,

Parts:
C19001, C19003, C19004: 100n; C_0603_1608Metric; LCSC C14663
C19002, C19005: 10u; C_0805_2012Metric; LCSC C15850
D19001: red; LED_0603_1608Metric; LCSC C2286
J19001: DS1024-2x6R2; LCSC C49284652
R19001: 13k; R_0603_1608Metric; LCSC C22797
R19002: 100k; R_0603_1608Metric; LCSC C25803
R19003: 330R; R_0603_1608Metric; LCSC C23138
SW19001: DSHP04TSGER; LCSC C3293144
TP19001: +3V3_PMODX; TestPoint_Pad_D1.5mm
U19001: SY6280AAC; LCSC C55136
U19002, U19003: TPD4E1U06; TPD4E1U06DBVR; LCSC C124691

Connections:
+3V3: C19001.1, C19002.1, SW19001.1, SW19001.3, SW19001.5, SW19001.7, U19001.5 (IN); also elsewhere on the board
+3V3_PMODX: C19003.1, C19004.1, C19005.1, D19001.2 (A), J19001.11, J19001.12, TP19001.1, U19001.1 (OUT)
/pmod_expansion/EN_PMODX: R19002.1, SW19001.8, U19001.4 (EN)
GND: C19001.2, C19002.2, C19003.2, C19004.2, C19005.2, J19001.9, J19001.10, R19001.2, R19002.2, R19003.2, U19001.2 (GND), U19002.2 (GND), U19003.2 (GND); also elsewhere on the board
unnamed: D19001.1 (K), R19003.1
unnamed: R19001.1, U19001.3 (ISET)
PMODX_IO1: J19001.1, U19002.1 (D1+); also elsewhere on the board
PMODX_IO2: J19001.3, U19002.3 (D2+); also elsewhere on the board
PMODX_IO3: J19001.5, U19002.6 (D1-); also elsewhere on the board
PMODX_IO4: J19001.7, U19002.4 (D2-); also elsewhere on the board
PMODX_IO5: J19001.2, U19003.1 (D1+); also elsewhere on the board
PMODX_IO6: J19001.4, U19003.3 (D2+); also elsewhere on the board
PMODX_IO7: J19001.6, U19003.6 (D1-); also elsewhere on the board
PMODX_IO8: J19001.8, U19003.4 (D2-); also elsewhere on the board
